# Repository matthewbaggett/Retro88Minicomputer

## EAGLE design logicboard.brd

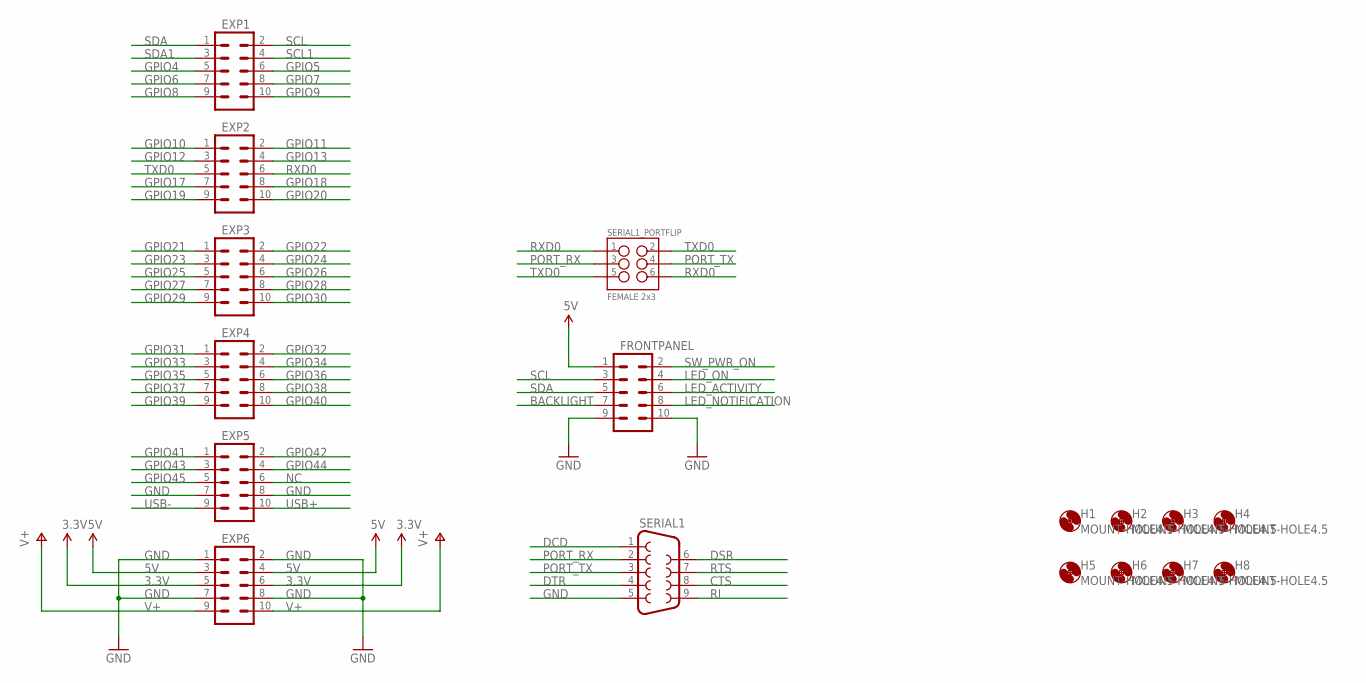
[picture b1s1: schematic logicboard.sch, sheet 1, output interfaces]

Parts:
EXP1, EXP2, EXP3, EXP4, EXP5, EXP6: M05X2SHD_LOCK; 2X5-SHROUDED_LOCK
FRONTPANEL: M05X2SHD_LOCK; 2X5-SHROUDED_LOCK
H1, H2, H3, H4, H5, H6, H7, H8: MOUNT-HOLE4.5; 4,5
SERIAL1: F09HP
SERIAL1_PORTFLIP: FEMALE 2x3; 2X3

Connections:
3.3V: EXP6.5, EXP6.6; also elsewhere on the board
5V: EXP6.3, EXP6.4, FRONTPANEL.1; also elsewhere on the board
BACKLIGHT: FRONTPANEL.7
CTS: SERIAL1.8
DCD: SERIAL1.1
DSR: SERIAL1.6
DTR: SERIAL1.4
GND: EXP5.7, EXP5.8, EXP6.1, EXP6.2, EXP6.7, EXP6.8, FRONTPANEL.9, FRONTPANEL.10, SERIAL1.5; also elsewhere on the board
GPIO4: EXP1.5; also elsewhere on the board
GPIO5: EXP1.6; also elsewhere on the board
GPIO6: EXP1.7; also elsewhere on the board
GPIO7: EXP1.8; also elsewhere on the board
GPIO8: EXP1.9; also elsewhere on the board
GPIO9: EXP1.10; also elsewhere on the board
GPIO10: EXP2.1; also elsewhere on the board
GPIO11: EXP2.2; also elsewhere on the board
GPIO12: EXP2.3; also elsewhere on the board
GPIO13: EXP2.4; also elsewhere on the board
GPIO17: EXP2.7; also elsewhere on the board
GPIO18: EXP2.8; also elsewhere on the board
GPIO19: EXP2.9; also elsewhere on the board
GPIO20: EXP2.10; also elsewhere on the board
GPIO21: EXP3.1; also elsewhere on the board
GPIO22: EXP3.2; also elsewhere on the board
GPIO23: EXP3.3; also elsewhere on the board
GPIO24: EXP3.4; also elsewhere on the board
GPIO25: EXP3.5; also elsewhere on the board
GPIO26: EXP3.6; also elsewhere on the board
GPIO27: EXP3.7; also elsewhere on the board
GPIO28: EXP3.8; also elsewhere on the board
GPIO29: EXP3.9; also elsewhere on the board
GPIO30: EXP3.10; also elsewhere on the board
GPIO31: EXP4.1; also elsewhere on the board
GPIO32: EXP4.2; also elsewhere on the board
GPIO33: EXP4.3; also elsewhere on the board
GPIO34: EXP4.4; also elsewhere on the board
GPIO35: EXP4.5; also elsewhere on the board
GPIO36: EXP4.6; also elsewhere on the board
GPIO37: EXP4.7; also elsewhere on the board
GPIO38: EXP4.8; also elsewhere on the board
GPIO39: EXP4.9; also elsewhere on the board
GPIO40: EXP4.10; also elsewhere on the board
GPIO41: EXP5.1; also elsewhere on the board
GPIO42: EXP5.2; also elsewhere on the board
GPIO43: EXP5.3; also elsewhere on the board
GPIO44: EXP5.4; also elsewhere on the board
GPIO45: EXP5.5; also elsewhere on the board
LED_ACTIVITY: FRONTPANEL.6
LED_NOTIFICATION: FRONTPANEL.8; also elsewhere on the board
LED_ON: FRONTPANEL.4
NC: EXP5.6
PORT_RX: SERIAL1.2, SERIAL1_PORTFLIP.3
PORT_TX: SERIAL1.3, SERIAL1_PORTFLIP.4
RI: SERIAL1.9
RTS: SERIAL1.7
RXD0: EXP2.6, SERIAL1_PORTFLIP.1, SERIAL1_PORTFLIP.6; also elsewhere on the board
SCL: EXP1.2, FRONTPANEL.3; also elsewhere on the board
SCL1: EXP1.4; also elsewhere on the board
SDA: EXP1.1, FRONTPANEL.5; also elsewhere on the board
SDA1: EXP1.3; also elsewhere on the board
SW_PWR_ON: FRONTPANEL.2
TXD0: EXP2.5, SERIAL1_PORTFLIP.2, SERIAL1_PORTFLIP.5; also elsewhere on the board
USB+: EXP5.10; also elsewhere on the board
USB-: EXP5.9; also elsewhere on the board
V+: EXP6.9, EXP6.10; also elsewhere on the board

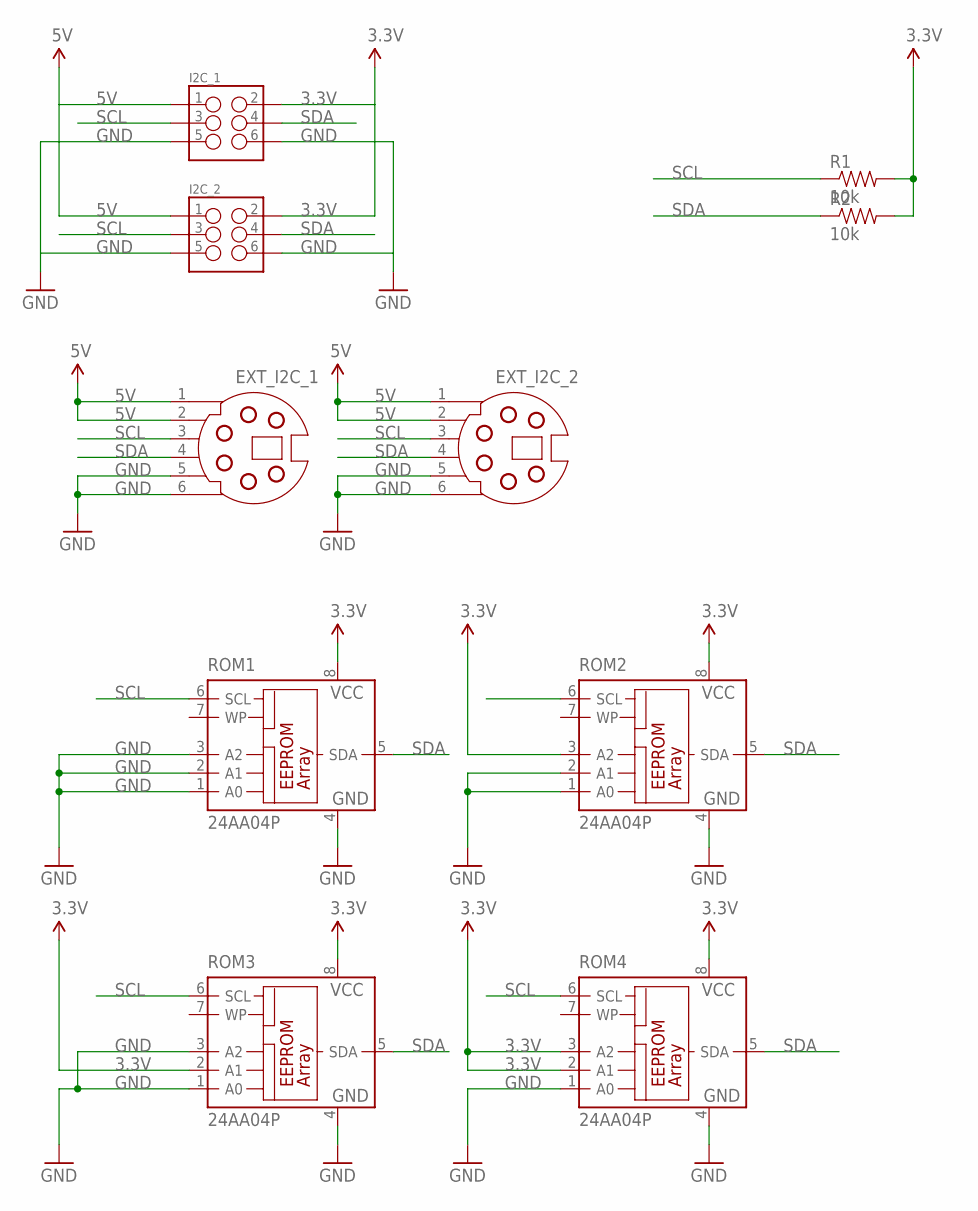
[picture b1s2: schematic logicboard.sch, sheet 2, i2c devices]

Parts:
EXT_I2C_1, EXT_I2C_2: MDSSV-BC06; SSV-BC06
I2C_1, I2C_2: M03X2SHROUD; 2X3-SHROUDED
R1, R2: 10k; AXIAL-0.3EZ
ROM1, ROM2, ROM3, ROM4: 24AA04P; DIL8

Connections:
3.3V: I2C_1.2, I2C_2.2, R1.P$2 (2), R2.P$2 (2), ROM1.8 (VCC), ROM2.3 (A2), ROM2.8 (VCC), ROM3.2 (A1), ROM3.8 (VCC), ROM4.2 (A1), ROM4.3 (A2), ROM4.8 (VCC); also elsewhere on the board
5V: EXT_I2C_1.1, EXT_I2C_1.2, EXT_I2C_2.1, EXT_I2C_2.2, I2C_1.1, I2C_2.1; also elsewhere on the board
GND: EXT_I2C_1.5, EXT_I2C_1.6, EXT_I2C_2.5, EXT_I2C_2.6, I2C_1.5, I2C_1.6, I2C_2.5, I2C_2.6, ROM1.1 (A0), ROM1.2 (A1), ROM1.3 (A2), ROM1.4 (GND), ROM2.1 (A0), ROM2.2 (A1), ROM2.4 (GND), ROM3.1 (A0), ROM3.3 (A2), ROM3.4 (GND), ROM4.1 (A0), ROM4.4 (GND); also elsewhere on the board
SCL: EXT_I2C_1.3, EXT_I2C_2.3, I2C_1.3, I2C_2.3, R1.P$1 (1), ROM1.6 (SCL), ROM2.6 (SCL), ROM3.6 (SCL), ROM4.6 (SCL); also elsewhere on the board
SDA: EXT_I2C_1.4, EXT_I2C_2.4, I2C_1.4, I2C_2.4, R2.P$1 (1), ROM1.5 (SDA), ROM2.5 (SDA), ROM3.5 (SDA), ROM4.5 (SDA); also elsewhere on the board

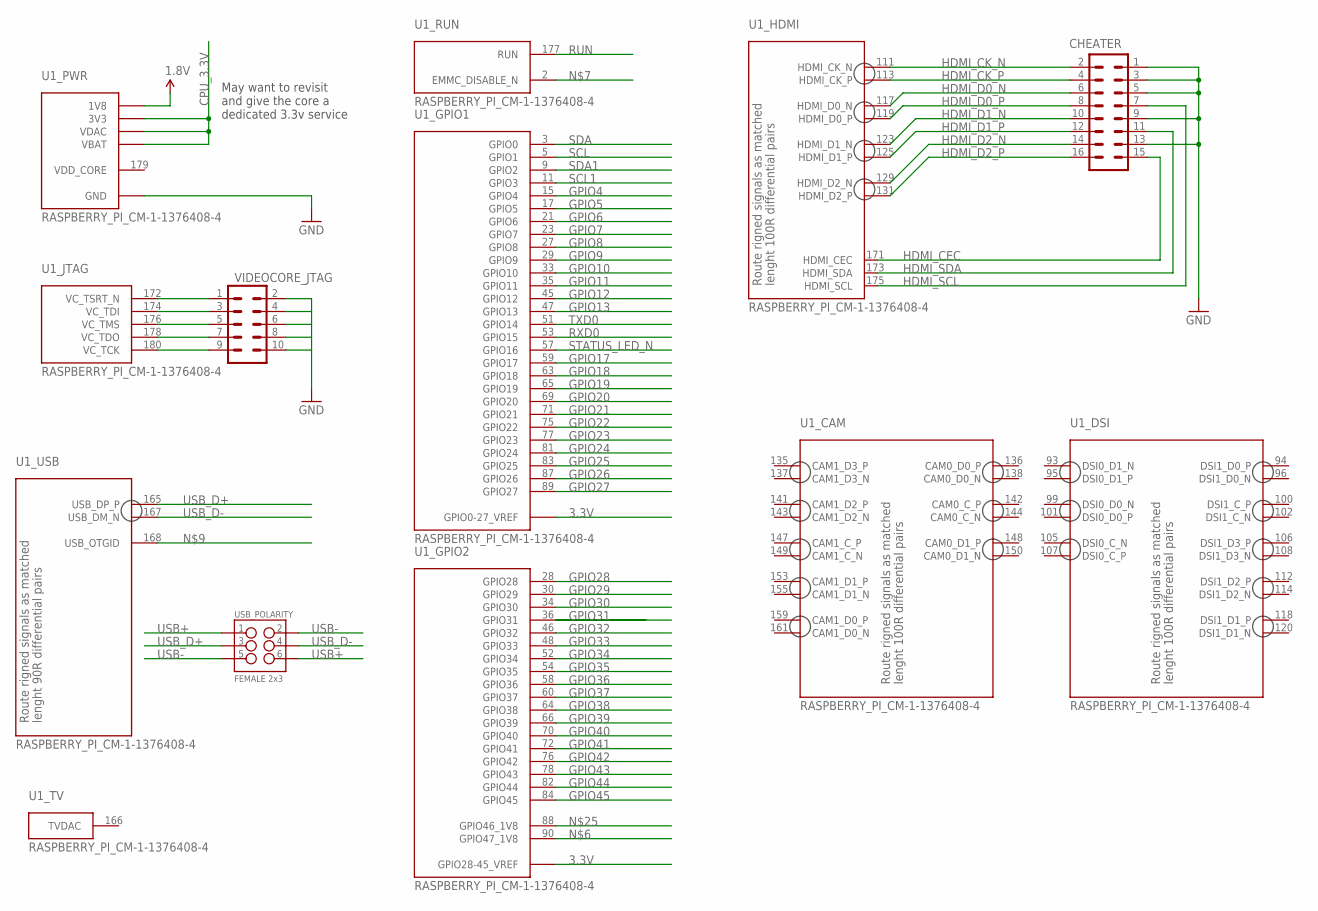
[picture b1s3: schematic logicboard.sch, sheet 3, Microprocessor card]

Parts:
CHEATER: M08X2; 2X8
U1: RASPBERRY_PI_CM-1-1376408-4; 1-1376408-4
USB_POLARITY: FEMALE 2x3; 2X3
VIDEOCORE_JTAG: M05X2SHD_LOCK; 2X5-SHROUDED_LOCK

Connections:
1.8V: U1.183 (1V8), U1.184 (1V8), U1.185 (1V8), U1.186 (1V8); also elsewhere on the board
3.3V: U1.39 (GPIO0-27_VREF), U1.40 (GPIO0-27_VREF), U1.41 (GPIO28-45_VREF), U1.42 (GPIO28-45_VREF); also elsewhere on the board
CPU_3.3V: U1.189 (VDAC), U1.190 (VDAC), U1.191 (3V3), U1.192 (3V3), U1.193 (3V3), U1.194 (3V3), U1.197 (VBAT), U1.198 (VBAT), U1.199 (VBAT), U1.200 (VBAT); also elsewhere on the board
GND: CHEATER.1, CHEATER.3, CHEATER.5, CHEATER.9, CHEATER.13, U1.1 (GND), U1.7 (GND), U1.13 (GND), U1.19 (GND), U1.25 (GND), U1.26 (GND), U1.31 (GND), U1.32 (GND), U1.37 (GND), U1.38 (GND), U1.43 (GND), U1.44 (GND), U1.49 (GND), U1.50 (GND), U1.55 (GND), U1.56 (GND), U1.61 (GND), U1.62 (GND), U1.67 (GND), U1.68 (GND), U1.73 (GND), U1.74 (GND), U1.79 (GND), U1.80 (GND), U1.85 (GND), U1.86 (GND), U1.91 (GND), U1.92 (GND), U1.97 (GND), U1.98 (GND), U1.103 (GND), U1.104 (GND), U1.109 (GND), U1.110 (GND), U1.115 (GND), U1.116 (GND), U1.121 (GND), U1.122 (GND), U1.127 (GND), U1.133 (GND), U1.134 (GND), U1.139 (GND), U1.140 (GND), U1.145 (GND), U1.146 (GND), U1.151 (GND), U1.152 (GND), U1.157 (GND), U1.163 (GND), U1.164 (GND), U1.169 (GND), U1.170 (GND), U1.181 (GND), U1.182 (GND), U1.187 (GND), U1.188 (GND), U1.195 (GND), U1.196 (GND), VIDEOCORE_JTAG.2, VIDEOCORE_JTAG.4, VIDEOCORE_JTAG.6, VIDEOCORE_JTAG.8, VIDEOCORE_JTAG.10; also elsewhere on the board
GPIO4: U1.15 (GPIO4); also elsewhere on the board
GPIO5: U1.17 (GPIO5); also elsewhere on the board
GPIO6: U1.21 (GPIO6); also elsewhere on the board
GPIO7: U1.23 (GPIO7); also elsewhere on the board
GPIO8: U1.27 (GPIO8); also elsewhere on the board
GPIO9: U1.29 (GPIO9); also elsewhere on the board
GPIO10: U1.33 (GPIO10); also elsewhere on the board
GPIO11: U1.35 (GPIO11); also elsewhere on the board
GPIO12: U1.45 (GPIO12); also elsewhere on the board
GPIO13: U1.47 (GPIO13); also elsewhere on the board
GPIO17: U1.59 (GPIO17); also elsewhere on the board
GPIO18: U1.63 (GPIO18); also elsewhere on the board
GPIO19: U1.65 (GPIO19); also elsewhere on the board
GPIO20: U1.69 (GPIO20); also elsewhere on the board
GPIO21: U1.71 (GPIO21); also elsewhere on the board
GPIO22: U1.75 (GPIO22); also elsewhere on the board
GPIO23: U1.77 (GPIO23); also elsewhere on the board
GPIO24: U1.81 (GPIO24); also elsewhere on the board
GPIO25: U1.83 (GPIO25); also elsewhere on the board
GPIO26: U1.87 (GPIO26); also elsewhere on the board
GPIO27: U1.89 (GPIO27); also elsewhere on the board
GPIO28: U1.28 (GPIO28); also elsewhere on the board
GPIO29: U1.30 (GPIO29); also elsewhere on the board
GPIO30: U1.34 (GPIO30); also elsewhere on the board
GPIO31: U1.36 (GPIO31); also elsewhere on the board
GPIO32: U1.46 (GPIO32); also elsewhere on the board
GPIO33: U1.48 (GPIO33); also elsewhere on the board
GPIO34: U1.52 (GPIO34); also elsewhere on the board
GPIO35: U1.54 (GPIO35); also elsewhere on the board
GPIO36: U1.58 (GPIO36); also elsewhere on the board
GPIO37: U1.60 (GPIO37); also elsewhere on the board
GPIO38: U1.64 (GPIO38); also elsewhere on the board
GPIO39: U1.66 (GPIO39); also elsewhere on the board
GPIO40: U1.70 (GPIO40); also elsewhere on the board
GPIO41: U1.72 (GPIO41); also elsewhere on the board
GPIO42: U1.76 (GPIO42); also elsewhere on the board
GPIO43: U1.78 (GPIO43); also elsewhere on the board
GPIO44: U1.82 (GPIO44); also elsewhere on the board
GPIO45: U1.84 (GPIO45); also elsewhere on the board
HDMI_CEC: CHEATER.15, U1.171 (HDMI_CEC)
HDMI_CK_N: CHEATER.2, U1.111 (HDMI_CK_N)
HDMI_CK_P: CHEATER.4, U1.113 (HDMI_CK_P)
HDMI_D0_N: CHEATER.6, U1.117 (HDMI_D0_N)
HDMI_D0_P: CHEATER.8, U1.119 (HDMI_D0_P)
HDMI_D1_N: CHEATER.10, U1.123 (HDMI_D1_N)
HDMI_D1_P: CHEATER.12, U1.125 (HDMI_D1_P)
HDMI_D2_N: CHEATER.14, U1.129 (HDMI_D2_N)
HDMI_D2_P: CHEATER.16, U1.131 (HDMI_D2_P)
HDMI_SCL: CHEATER.7, U1.175 (HDMI_SCL)
HDMI_SDA: CHEATER.11, U1.173 (HDMI_SDA)
unnamed: U1.180 (VC_TCK), VIDEOCORE_JTAG.9
unnamed: U1.178 (VC_TDO), VIDEOCORE_JTAG.7
unnamed: U1.176 (VC_TMS), VIDEOCORE_JTAG.5
unnamed: U1.174 (VC_TDI), VIDEOCORE_JTAG.3
unnamed: U1.172 (VC_TSRT_N), VIDEOCORE_JTAG.1
RUN: U1.177 (RUN)
RXD0: U1.53 (GPIO15); also elsewhere on the board
SCL: U1.5 (GPIO1); also elsewhere on the board
SCL1: U1.11 (GPIO3); also elsewhere on the board
SDA: U1.3 (GPIO0); also elsewhere on the board
SDA1: U1.9 (GPIO2); also elsewhere on the board
STATUS_LED_N: U1.57 (GPIO16)
TXD0: U1.51 (GPIO14); also elsewhere on the board
USB+: USB_POLARITY.1, USB_POLARITY.6; also elsewhere on the board
USB-: USB_POLARITY.2, USB_POLARITY.5; also elsewhere on the board
USB_D+: U1.165 (USB_DP_P), USB_POLARITY.3
USB_D-: U1.167 (USB_DM_N), USB_POLARITY.4

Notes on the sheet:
May want to revisit and give the core a dedicated 3.3v service

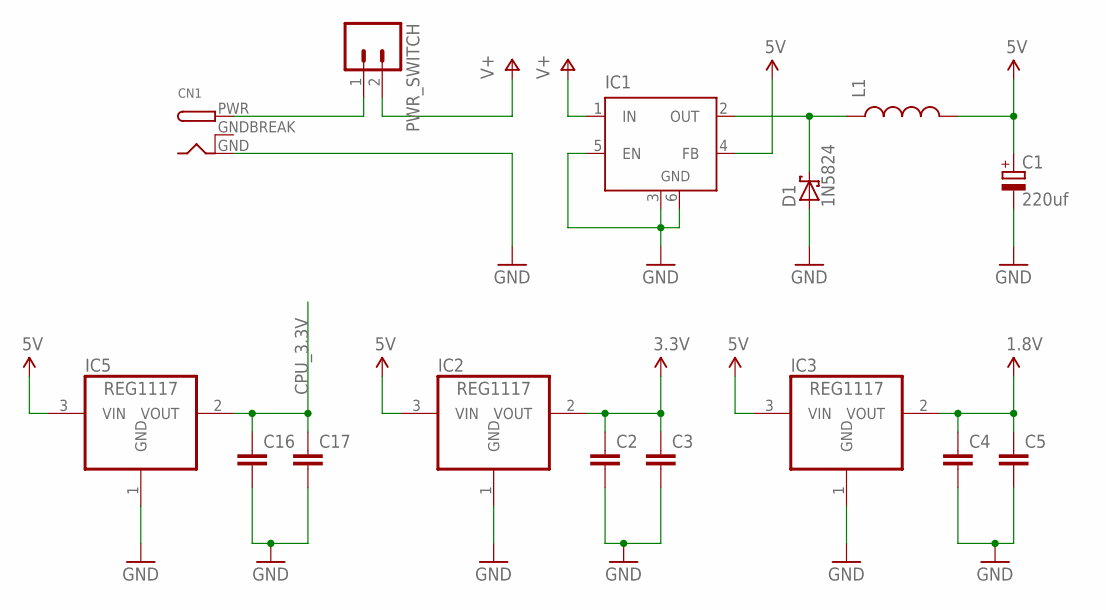
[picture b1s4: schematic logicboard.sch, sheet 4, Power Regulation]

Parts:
C1: 220uf; E2,5-6
C2, C3, C4, C5, C16, C17: CAP1206; 1206
CN1: DCBARRELPTH; DCJACK_2MM_PTH
D1: 1N5824; DO41-7.6
IC1: LM2596S; TO263-5
IC2, IC3, IC5: REG1117; SOT223
L1: INDUCTORSRU1038; SRU1038
PWR_SWITCH: M02POLAR; MOLEX-1X2

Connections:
1.8V: C4.1, C5.1, IC3.2 (VOUT); also elsewhere on the board
3.3V: C2.1, C3.1, IC2.2 (VOUT); also elsewhere on the board
5V: C1.+, IC1.4 (FB), IC2.3 (VIN), IC3.3 (VIN), IC5.3 (VIN), L1.2; also elsewhere on the board
CPU_3.3V: C16.1, C17.1, IC5.2 (VOUT); also elsewhere on the board
GND: C1.-, C2.2, C3.2, C4.2, C5.2, C16.2, C17.2, CN1.GND, D1.A, IC1.3 (GND), IC1.5 (EN), IC1.6 (GND), IC2.1 (GND), IC3.1 (GND), IC5.1 (GND); also elsewhere on the board
GNDBREAK: CN1.GNDBREAK
unnamed: CN1.PWR, PWR_SWITCH.1
V+: IC1.1 (IN), PWR_SWITCH.2; also elsewhere on the board
VOUT: D1.C, IC1.2 (OUT), L1.1

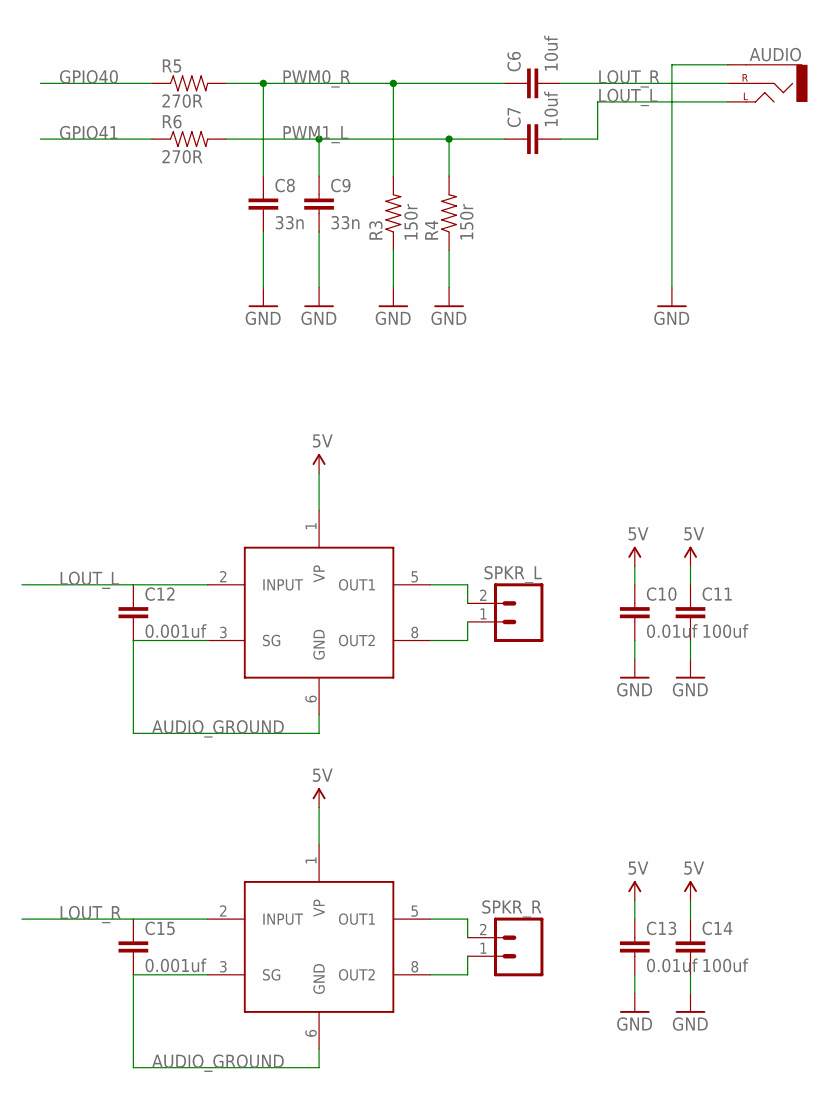
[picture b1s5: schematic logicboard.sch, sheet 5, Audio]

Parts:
AUDIO: AUDIO-JACKPTH; AUDIO-JACK
C6, C7: 10uf; CAP-PTH-SMALLEZ
C8, C9: 33n; CAP-PTH-SMALLEZ
C10, C13: 0.01uf; CAP-PTH-SMALLEZ
C11, C14: 100uf; CAP-PTH-SMALLEZ
C12, C15: 0.001uf; CAP-PTH-SMALLEZ
R3, R4: 150r; AXIAL-0.3EZ
R5, R6: 270R; AXIAL-0.3EZ
SPKR_L: M02JST-PTH-2-KIT; JST-2-PTH-KIT
SPKR_R: M02JST-PTH-2-KIT; JST-2-PTH-KIT
U$1, U$2: TDA7052; DIL08

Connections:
5V: C10.1, C11.1, C13.1, C14.1, U$1.1 (VP), U$2.1 (VP); also elsewhere on the board
AUDIO_GROUND: C12.2, C15.2, U$1.3 (SG), U$1.6 (GND), U$2.3 (SG), U$2.6 (GND); also elsewhere on the board
GND: AUDIO.SLEEVE, C8.2, C9.2, C10.2, C11.2, C13.2, C14.2, R3.P$1 (1), R4.P$1 (1); also elsewhere on the board
GPIO40: R5.P$1 (1); also elsewhere on the board
GPIO41: R6.P$1 (1); also elsewhere on the board
LOUT_L: AUDIO.TIP (LEFT), C7.2, C12.1, U$1.2 (INPUT)
LOUT_R: AUDIO.RING (RIGHT), C6.2, C15.1, U$2.2 (INPUT)
unnamed: SPKR_L.2, U$1.5 (OUT1)
unnamed: SPKR_L.1, U$1.8 (OUT2)
unnamed: SPKR_R.2, U$2.5 (OUT1)
unnamed: SPKR_R.1, U$2.8 (OUT2)
PWM0_R: C6.1, C8.1, R3.P$2 (2), R5.P$2 (2)
PWM1_L: C7.1, C9.1, R4.P$2 (2), R6.P$2 (2)

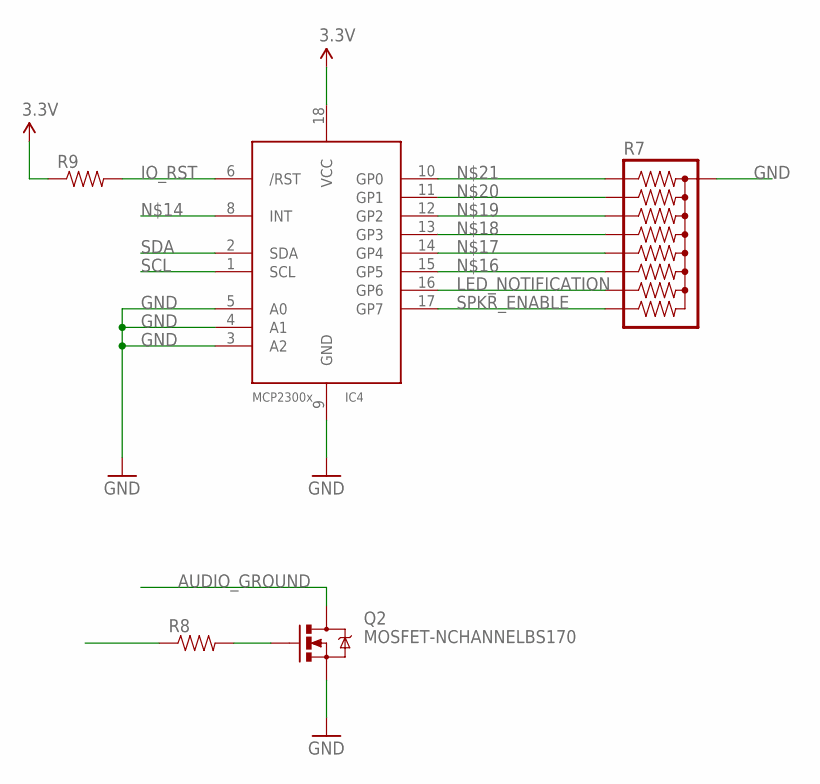
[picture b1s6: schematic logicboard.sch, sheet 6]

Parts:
IC4: MCP2300X/P; DIL18
Q2: MOSFET-NCHANNELBS170; TO-92
R7: RPACK-BUSSED-8-SIP-PTH-8; RPACK-SIP-PTH-8
R8, R9: RESISTOREZ; AXIAL-0.3EZ

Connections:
3.3V: IC4.18 (VCC), R9.P$1 (1); also elsewhere on the board
AUDIO_GROUND: Q2.1 (D); also elsewhere on the board
GND: IC4.3 (A2), IC4.4 (A1), IC4.5 (A0), IC4.9 (GND), Q2.3 (S), R7.P$1 (1); also elsewhere on the board
IO_RST: IC4.6 (/RST), R9.P$2 (2)
LED_NOTIFICATION: IC4.16 (GP6), R7.P$8 (8); also elsewhere on the board
unnamed: Q2.2 (G), R8.P$2 (2)
unnamed: IC4.15 (GP5), R7.P$7 (7)
unnamed: IC4.14 (GP4), R7.P$6 (6)
unnamed: IC4.13 (GP3), R7.P$5 (5)
unnamed: IC4.12 (GP2), R7.P$4 (4)
unnamed: IC4.11 (GP1), R7.P$3 (3)
unnamed: IC4.10 (GP0), R7.P$2 (2)
SCL: IC4.1 (SCL); also elsewhere on the board
SDA: IC4.2 (SDA); also elsewhere on the board
SPKR_ENABLE: IC4.17 (GP7), R7.P$9 (9), R8.P$1 (1)

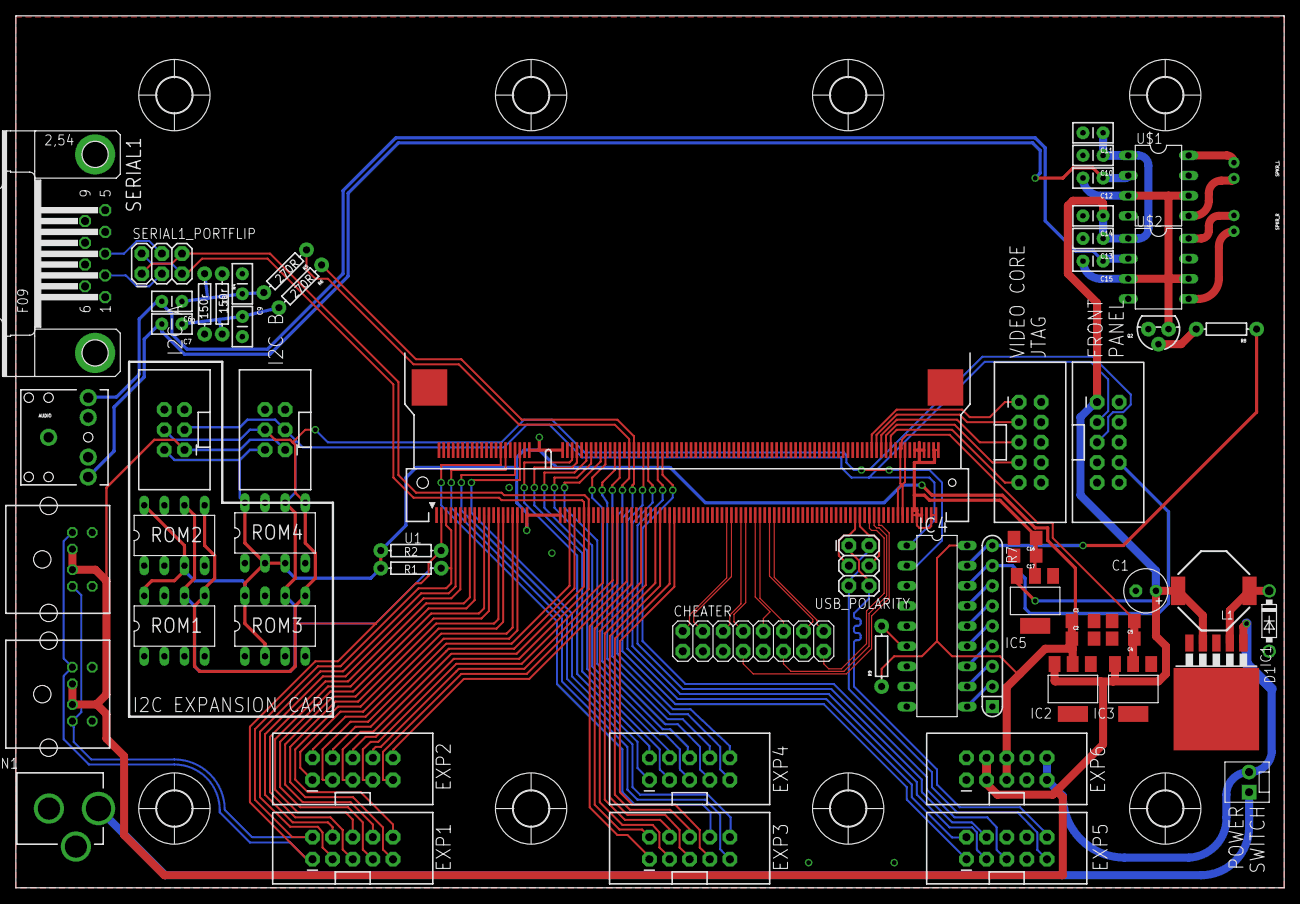
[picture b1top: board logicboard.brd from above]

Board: 2 copper layers, 160.0 x 110.0 mm, 70 parts (0 on the bottom side), 94 nets.

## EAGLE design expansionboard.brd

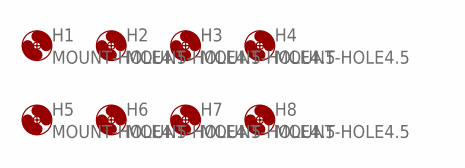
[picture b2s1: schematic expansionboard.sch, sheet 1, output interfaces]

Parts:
H1, H2, H3, H4, H5, H6, H7, H8: MOUNT-HOLE4.5; 4,5

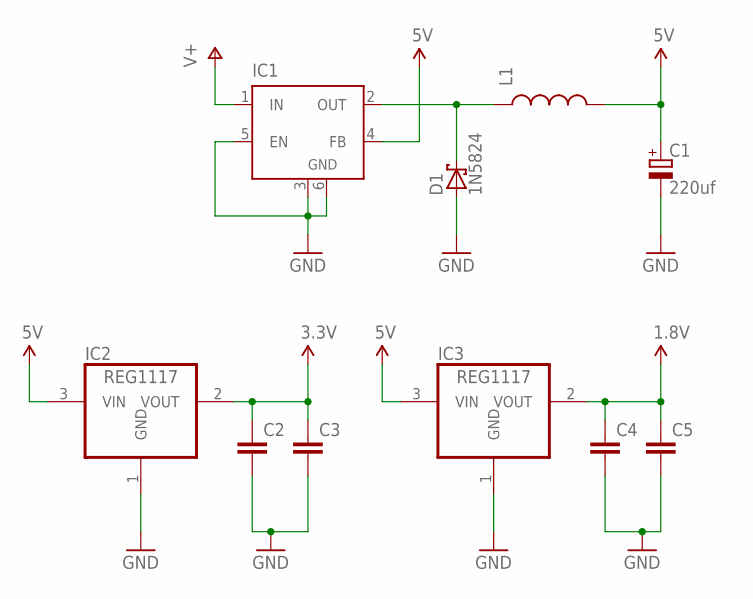
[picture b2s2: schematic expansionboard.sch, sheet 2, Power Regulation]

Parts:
C1: 220uf; E2,5-6
C2, C3, C4, C5: CAP1206; 1206
D1: 1N5824; DO41-7.6
IC1: LM2596S; TO263-5
IC2, IC3: REG1117; SOT223
L1: INDUCTORSRU1038; SRU1038

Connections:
1.8V: C4.1, C5.1, IC3.2 (VOUT)
3.3V: C2.1, C3.1, IC2.2 (VOUT); also elsewhere on the board
5V: C1.+, IC1.4 (FB), IC2.3 (VIN), IC3.3 (VIN), L1.2; also elsewhere on the board
GND: C1.-, C2.2, C3.2, C4.2, C5.2, D1.A, IC1.3 (GND), IC1.5 (EN), IC1.6 (GND), IC2.1 (GND), IC3.1 (GND); also elsewhere on the board
V+: IC1.1 (IN); also elsewhere on the board
VOUT: D1.C, IC1.2 (OUT), L1.1

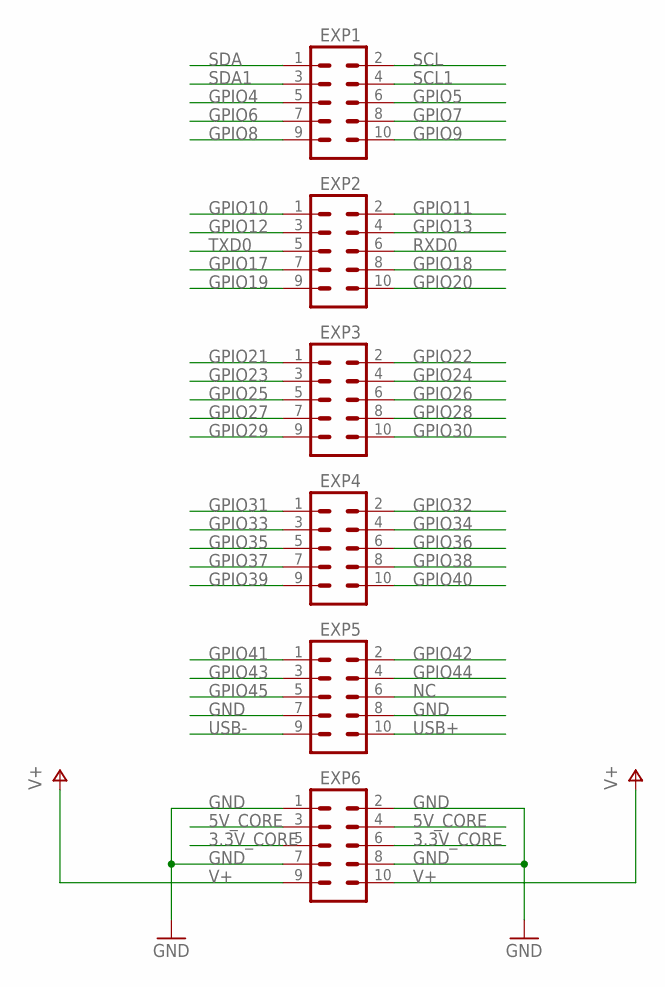
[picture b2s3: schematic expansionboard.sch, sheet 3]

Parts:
EXP1, EXP2, EXP3, EXP4, EXP5, EXP6: M05X2SHD_LOCK; 2X5-SHROUDED_LOCK

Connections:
3.3V_CORE: EXP6.5, EXP6.6
5V_CORE: EXP6.3, EXP6.4
GND: EXP5.7, EXP5.8, EXP6.1, EXP6.2, EXP6.7, EXP6.8; also elsewhere on the board
GPIO4: EXP1.5; also elsewhere on the board
GPIO5: EXP1.6; also elsewhere on the board
GPIO6: EXP1.7; also elsewhere on the board
GPIO7: EXP1.8; also elsewhere on the board
GPIO8: EXP1.9; also elsewhere on the board
GPIO9: EXP1.10; also elsewhere on the board
GPIO10: EXP2.1; also elsewhere on the board
GPIO11: EXP2.2; also elsewhere on the board
GPIO12: EXP2.3; also elsewhere on the board
GPIO13: EXP2.4; also elsewhere on the board
GPIO17: EXP2.7; also elsewhere on the board
GPIO18: EXP2.8; also elsewhere on the board
GPIO19: EXP2.9; also elsewhere on the board
GPIO20: EXP2.10; also elsewhere on the board
GPIO21: EXP3.1; also elsewhere on the board
GPIO22: EXP3.2; also elsewhere on the board
GPIO23: EXP3.3; also elsewhere on the board
GPIO24: EXP3.4; also elsewhere on the board
GPIO25: EXP3.5; also elsewhere on the board
GPIO26: EXP3.6; also elsewhere on the board
GPIO27: EXP3.7; also elsewhere on the board
GPIO28: EXP3.8; also elsewhere on the board
GPIO29: EXP3.9; also elsewhere on the board
GPIO30: EXP3.10; also elsewhere on the board
GPIO31: EXP4.1; also elsewhere on the board
GPIO32: EXP4.2; also elsewhere on the board
GPIO33: EXP4.3; also elsewhere on the board
GPIO34: EXP4.4; also elsewhere on the board
GPIO35: EXP4.5; also elsewhere on the board
GPIO36: EXP4.6; also elsewhere on the board
GPIO37: EXP4.7; also elsewhere on the board
GPIO38: EXP4.8; also elsewhere on the board
GPIO39: EXP4.9; also elsewhere on the board
GPIO40: EXP4.10; also elsewhere on the board
GPIO41: EXP5.1; also elsewhere on the board
GPIO42: EXP5.2; also elsewhere on the board
GPIO43: EXP5.3; also elsewhere on the board
GPIO44: EXP5.4; also elsewhere on the board
GPIO45: EXP5.5; also elsewhere on the board
NC: EXP5.6
RXD0: EXP2.6; also elsewhere on the board
SCL: EXP1.2; also elsewhere on the board
SCL1: EXP1.4; also elsewhere on the board
SDA: EXP1.1; also elsewhere on the board
SDA1: EXP1.3; also elsewhere on the board
TXD0: EXP2.5; also elsewhere on the board
USB+: EXP5.10; also elsewhere on the board
USB-: EXP5.9; also elsewhere on the board
V+: EXP6.9, EXP6.10; also elsewhere on the board

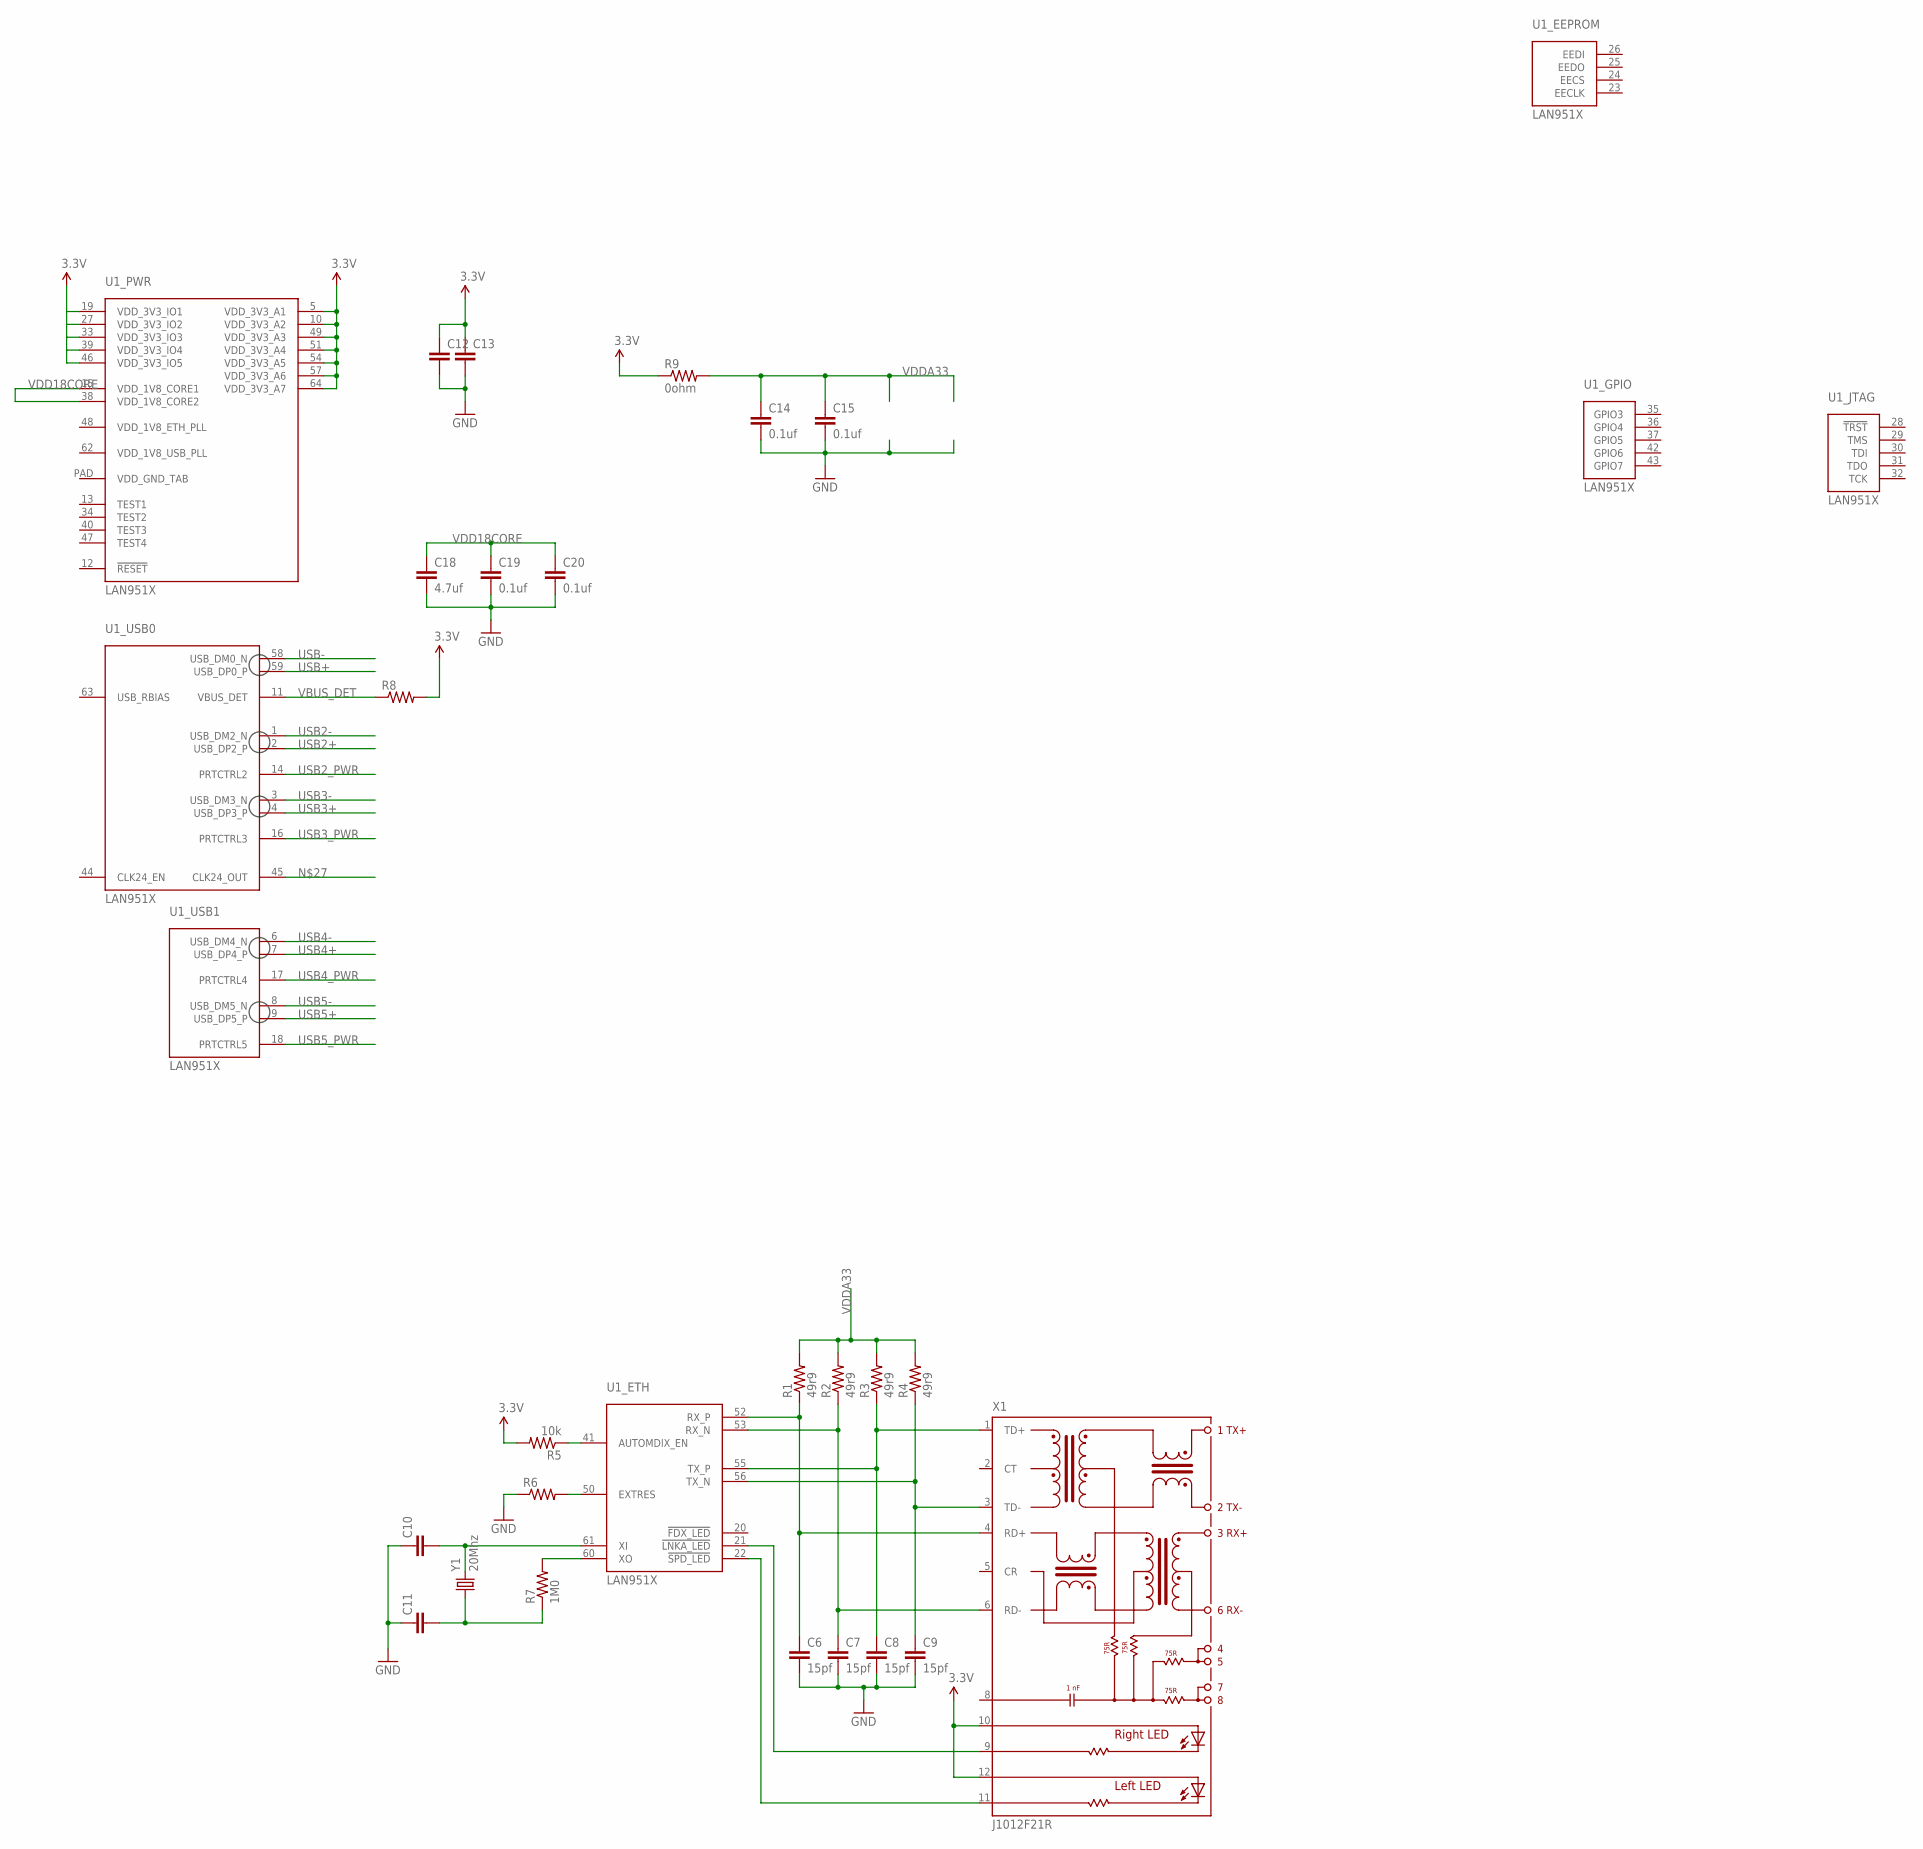
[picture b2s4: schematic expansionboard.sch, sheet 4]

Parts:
C6, C7, C8, C9: 15pf; CAP-PTH-SMALLEZ
C10, C11, C12, C13: CAPEZ; CAP-PTH-SMALLEZ
C14, C15, C19, C20: 0.1uf; 1206
C18: 4.7uf; 1206
R1, R2, R3, R4: 49r9; AXIAL-0.3EZ
R5: 10k; AXIAL-0.3EZ
R6: RESISTOREZ; AXIAL-0.3EZ
R7: 1M0; AXIAL-0.3EZ
R8: RESISTOR1206; 1206
R9: 0ohm; 1206
U1: LAN951X; QFN-64
X1: J1012F21R; J1
Y1: 20Mhz; HC49US

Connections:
3.3V: C12.1, C13.1, R5.P$2 (2), R8.2, R9.1, U1.5 (VDD_3V3_A1), U1.10 (VDD_3V3_A2), U1.19 (VDD_3V3_IO1), U1.27 (VDD_3V3_IO2), U1.33 (VDD_3V3_IO3), U1.39 (VDD_3V3_IO4), U1.46 (VDD_3V3_IO5), U1.49 (VDD_3V3_A3), U1.51 (VDD_3V3_A4), U1.54 (VDD_3V3_A5), U1.57 (VDD_3V3_A6), U1.64 (VDD_3V3_A7), X1.10 (A-R), X1.12 (A-L); also elsewhere on the board
GND: C6.2, C7.2, C8.2, C9.2, C10.1, C11.1, C12.2, C13.2, C14.2, C15.2, C18.2, C19.2, C20.2, R6.P$1 (1); also elsewhere on the board
unnamed: C6.1, R1.P$1 (1), U1.52 (RX_P), X1.4 (RD+)
unnamed: C7.1, R2.P$1 (1), U1.53 (RX_N), X1.6 (RD-)
unnamed: C8.1, R3.P$1 (1), U1.55 (TX_P), X1.1 (TD+)
unnamed: C9.1, R4.P$1 (1), U1.56 (TX_N), X1.3 (TD-)
unnamed: U1.21 (!LNKA_LED), X1.9 (C-R)
unnamed: U1.22 (!SPD_LED), X1.11 (C-L)
unnamed: R5.P$1 (1), U1.41 (AUTOMDIX_EN)
unnamed: R6.P$2 (2), U1.50 (EXTRES)
unnamed: C10.2, U1.61 (XI), Y1.2
unnamed: C11.2, R7.P$1 (1), Y1.1
unnamed: R7.P$2 (2), U1.60 (XO)
USB2+: U1.2 (USB_DP2_P); also elsewhere on the board
USB2-: U1.1 (USB_DM2_N); also elsewhere on the board
USB2_PWR: U1.14 (PRTCTRL2); also elsewhere on the board
USB3+: U1.4 (USB_DP3_P); also elsewhere on the board
USB3-: U1.3 (USB_DM3_N); also elsewhere on the board
USB3_PWR: U1.16 (PRTCTRL3); also elsewhere on the board
USB4+: U1.7 (USB_DP4_P); also elsewhere on the board
USB4-: U1.6 (USB_DM4_N); also elsewhere on the board
USB4_PWR: U1.17 (PRTCTRL4); also elsewhere on the board
USB5+: U1.9 (USB_DP5_P); also elsewhere on the board
USB5-: U1.8 (USB_DM5_N); also elsewhere on the board
USB5_PWR: U1.18 (PRTCTRL5); also elsewhere on the board
USB+: U1.59 (USB_DP0_P); also elsewhere on the board
USB-: U1.58 (USB_DM0_N); also elsewhere on the board
VBUS_DET: R8.1, U1.11 (VBUS_DET)
VDD18CORE: C18.1, C19.1, C20.1, U1.15 (VDD_1V8_CORE1), U1.38 (VDD_1V8_CORE2)
VDDA33: C14.1, C15.1, R1.P$2 (2), R2.P$2 (2), R3.P$2 (2), R4.P$2 (2), R9.2

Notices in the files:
parts and their libraries:
SparkFun-Capacitors: Licensing: Creative Commons ShareAlike 4.0 International - https://creativecommons.org/licenses/by-sa/4.0
